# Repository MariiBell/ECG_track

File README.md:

# ECG Tracker
---

KiCad8_project : KiCad 8.0 project with PCB design for LUT  

Case_3dmodels : 3d models of case in .step format  

model : folder with neural network (LSTM-based autoencoder) and notebook for its training  

ECG_track.py : class for ECG tracking realizing Interface.py  
socket_.py : PC program  
main.py : micropython program for ESP32

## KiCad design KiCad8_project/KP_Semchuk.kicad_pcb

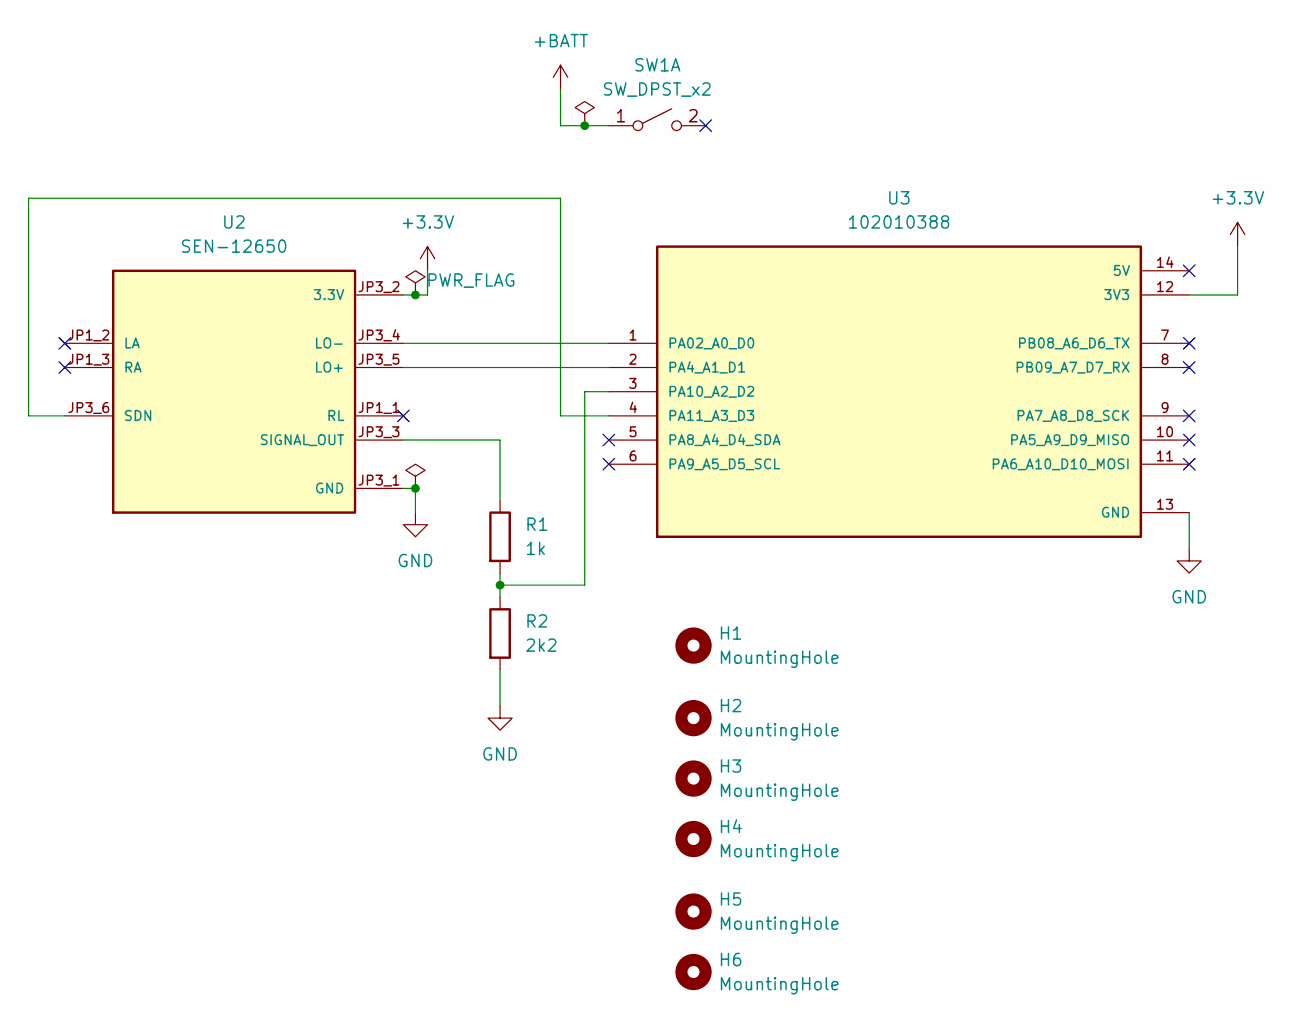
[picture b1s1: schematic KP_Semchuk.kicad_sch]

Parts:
H1, H2, H3, H4, H5, H6: MountingHole; MountingHole_3.2mm_M3
R1: 1k; R_Axial_DIN0207_L6.3mm_D2.5mm_P7.62mm_Horizontal
R2: 2k2; R_Axial_DIN0207_L6.3mm_D2.5mm_P7.62mm_Horizontal
SW1: SW_DPST_x2; SW_DIP_SPSTx01_Slide_9.78x4.72mm_W7.62mm_P2.54mm
U2: SEN-12650; MODULE_SEN-12650; PARTREV V10
U3: 102010388; MODULE_102010388; PARTREV N/A

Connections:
+3.3V: U2.JP3_2 (3.3V), U3.12 (3V3)
+BATT: SW1.1 (A)
GND: R2.2, U2.JP3_1 (GND), U3.13 (GND)
unnamed: U2.JP3_5 (LO+), U3.2 (PA4_A1_D1)
unnamed: U2.JP3_4 (LO-), U3.1 (PA02_A0_D0)
unnamed: U2.JP3_6 (SDN), U3.4 (PA11_A3_D3)
unnamed: R1.1, U2.JP3_3 (SIGNAL_OUT)
unnamed: R1.2, R2.1, U3.3 (PA10_A2_D2)

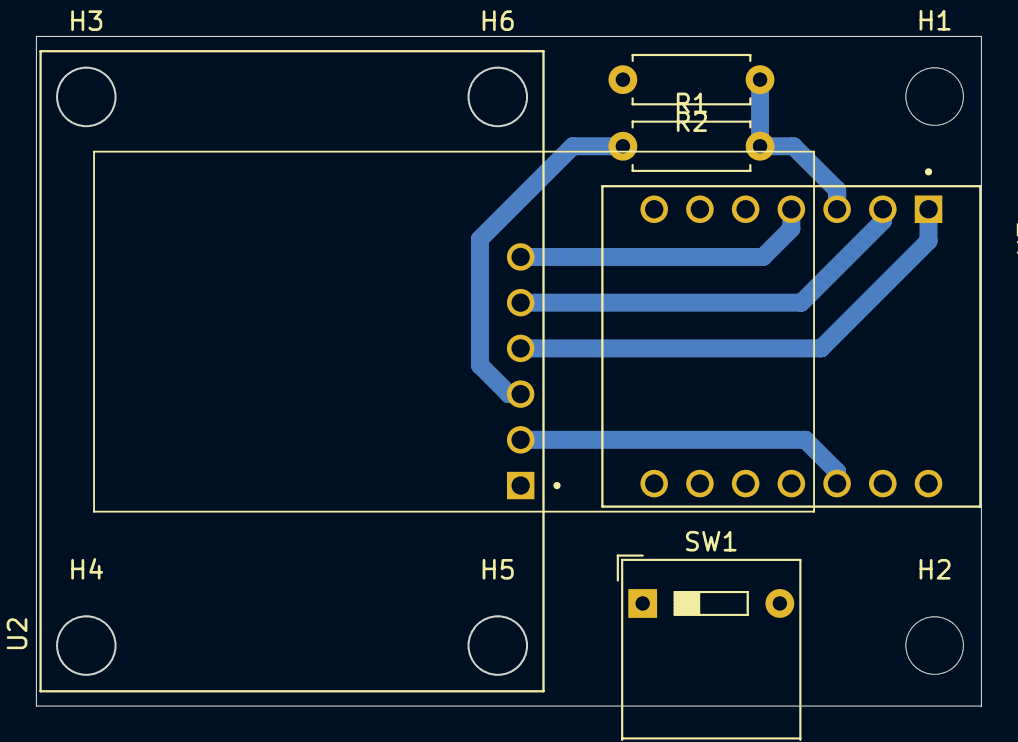
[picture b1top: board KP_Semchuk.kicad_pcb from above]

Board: 2 copper layers, 52.5 x 37.2 mm, 11 parts (0 on the bottom side), 7 nets.

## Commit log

2024-06-25 second commit
2024-06-25 third commit
2024-06-25 main modified
2024-06-28 commit2806
2024-06-28 commit2806_2
